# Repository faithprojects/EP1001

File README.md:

# Singapore Polytechnic EP1001 - Further Digital Fabrication & Prototyping Elective Module
Project Website Documentation for EP1001 <br>
A documentation of my school assignments, final project and my journey in undertaking my elective module. <br>
Website link: https://faithprojects.github.io/EP1001/

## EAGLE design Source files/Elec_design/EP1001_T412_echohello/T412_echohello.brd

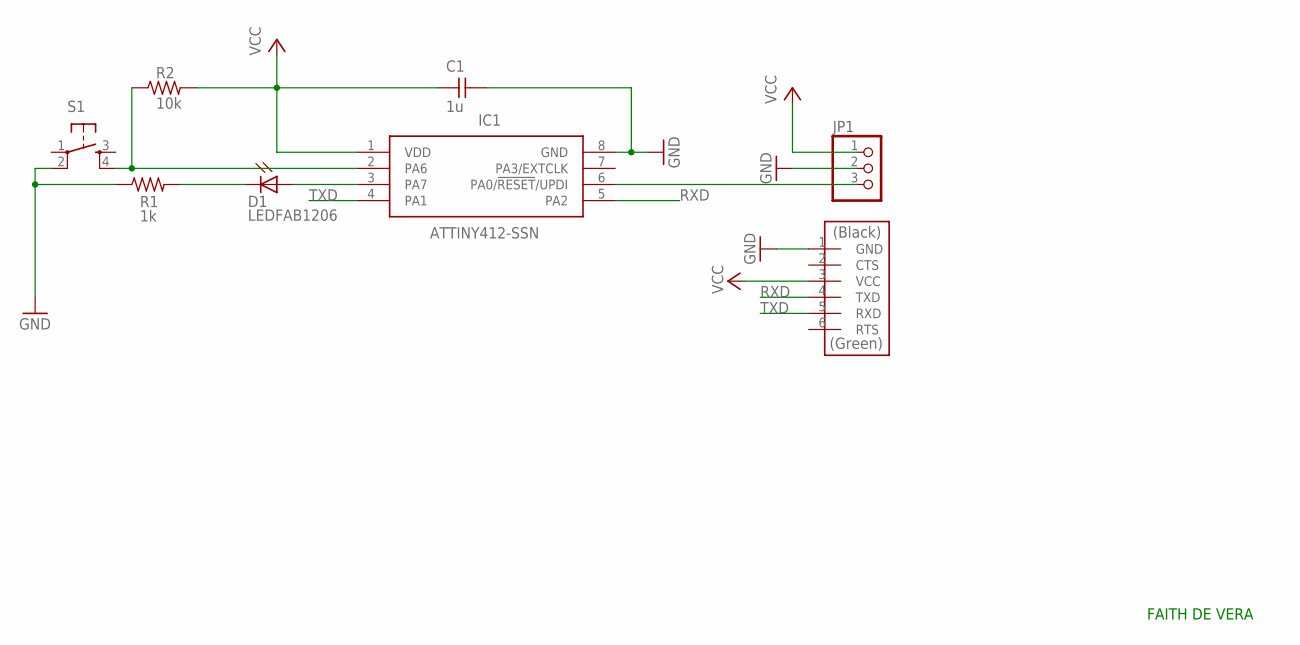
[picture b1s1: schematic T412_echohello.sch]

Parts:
C1: 1u; C1206FAB
D1: LEDFAB1206; LED1206FAB
IC1: ATTINY412-SSN; SOIC127P600X175-8N
JP1: PINHD-1X3; 1X03
R1: 1k; R1206FAB
R2: 10k; R1206FAB
S1: SW_SWITCH_TACTILE_6MM6MM_SWITCH; 6MM_SWITCH
U$2: CONN_06_FTDI-SMD-HEADER; 1X06SMD

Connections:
GND: C1.2, IC1.8 (GND), JP1.2, R1.1, S1.2 (P1), U$2.1 (GND)
unnamed: D1.1 (A), IC1.3 (PA7)
unnamed: D1.2 (C), R1.2
unnamed: IC1.2 (PA6), R2.1, S1.4 (S1)
unnamed: IC1.6 (PA0/!RESET!/UPDI), JP1.3
RXD: IC1.5 (PA2), U$2.4 (TXD)
TXD: IC1.4 (PA1), U$2.5 (RXD)
VCC: C1.1, IC1.1 (VDD), JP1.1, R2.2, U$2.3 (VCC)

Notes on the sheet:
FAITH DE VERA

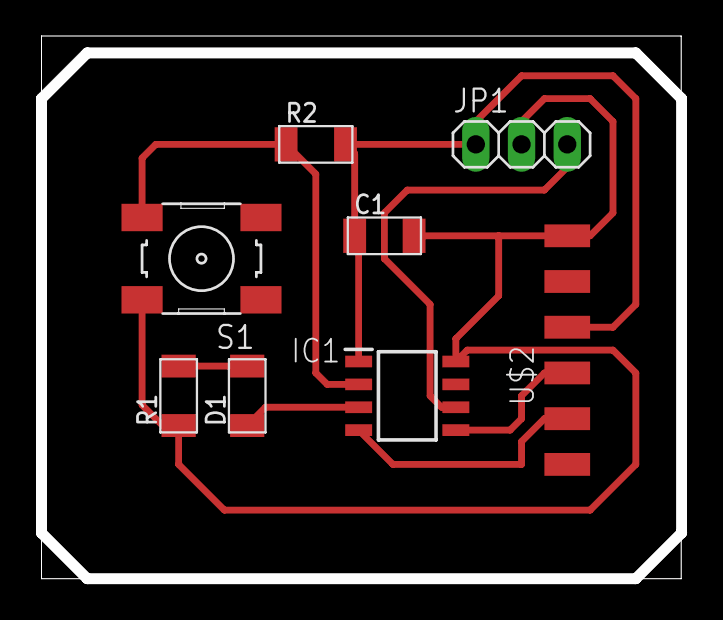
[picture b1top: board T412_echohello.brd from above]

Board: 2 copper layers, 35.5 x 30.1 mm, 8 parts (0 on the bottom side), 8 nets.

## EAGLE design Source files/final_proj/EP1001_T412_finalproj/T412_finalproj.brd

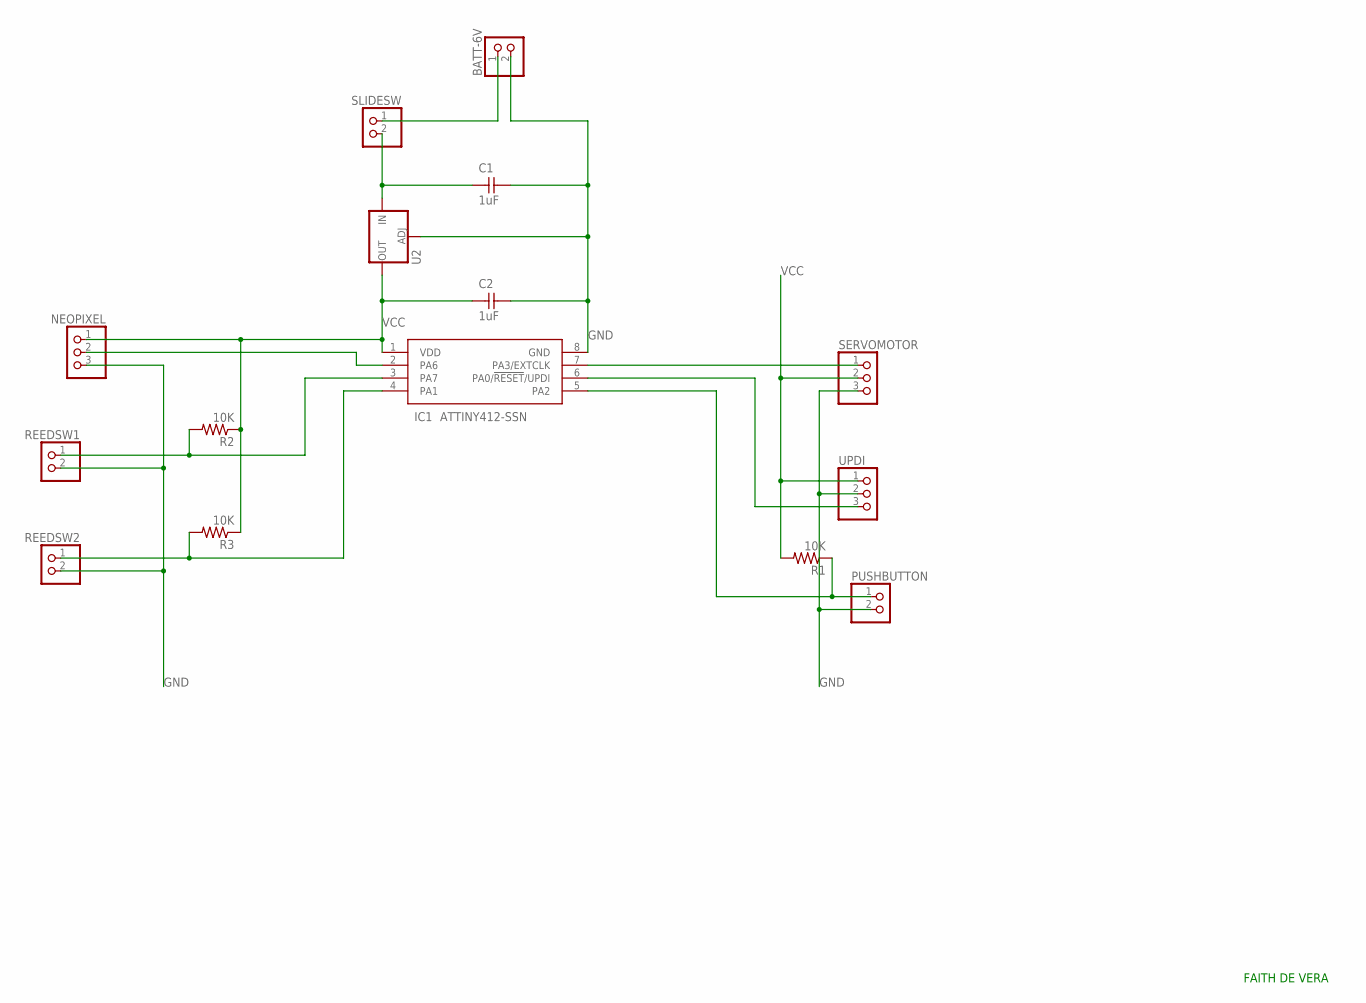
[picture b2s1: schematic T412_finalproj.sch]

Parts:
BATT-6V: PINHD-1X2; 1X02
C1, C2: 1uF; C1206FAB
IC1: ATTINY412-SSN; SOIC127P600X175-8N
NEOPIXEL: PINHD-1X3; 1X03
PUSHBUTTON: PINHD-1X2; 1X02
R1, R2, R3: 10K; R1206FAB
REEDSW1, REEDSW2: PINHD-1X2; 1X02
SERVOMOTOR: PINHD-1X3; 1X03
SLIDESW: PINHD-1X2; 1X02
U2: V_REG_LM1117SOT223; SOT223
UPDI: PINHD-1X3; 1X03

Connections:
GND: BATT-6V.2, C1.2, C2.2, IC1.8 (GND), NEOPIXEL.3, PUSHBUTTON.2, REEDSW1.2, REEDSW2.2, SERVOMOTOR.3, U2.1 (ADJ), UPDI.2
unnamed: IC1.5 (PA2), PUSHBUTTON.1, R1.1
unnamed: IC1.3 (PA7), R2.2, REEDSW1.1
unnamed: IC1.4 (PA1), R3.2, REEDSW2.1
unnamed: IC1.7 (PA3/EXTCLK), SERVOMOTOR.1
unnamed: IC1.6 (PA0/!RESET!/UPDI), UPDI.3
unnamed: C1.1, SLIDESW.2, U2.3 (IN)
unnamed: BATT-6V.1, SLIDESW.1
unnamed: IC1.2 (PA6), NEOPIXEL.2
VCC: C2.1, IC1.1 (VDD), NEOPIXEL.1, R1.2, R2.1, R3.1, SERVOMOTOR.2, U2.2 (OUT), U2.4 (OUT), UPDI.1

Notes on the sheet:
FAITH DE VERA

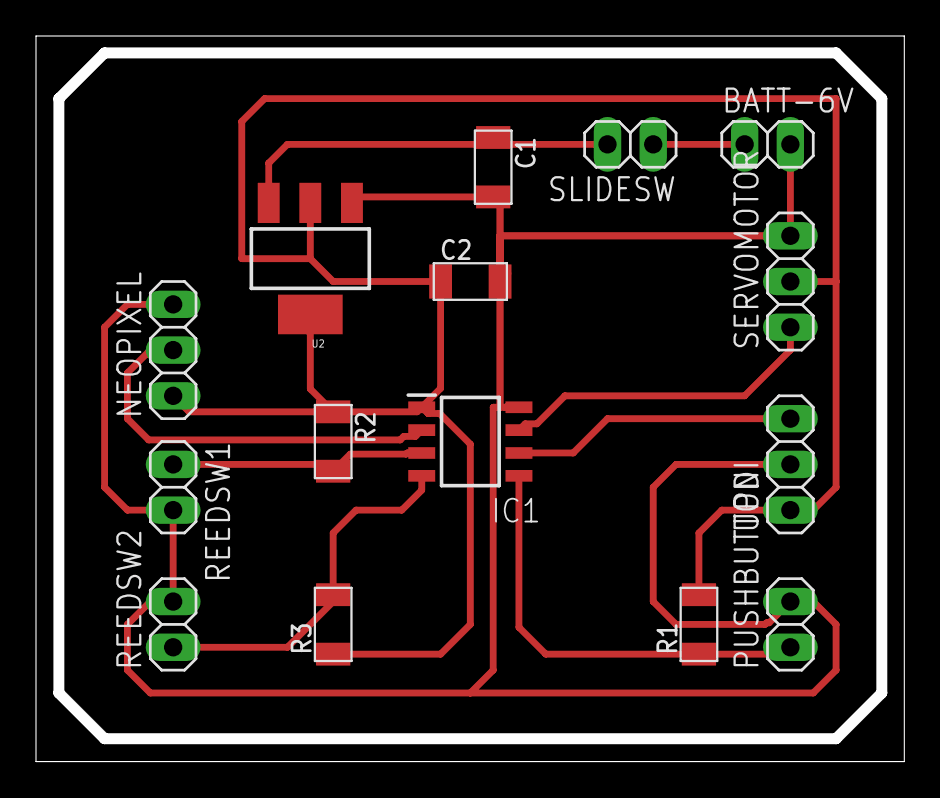
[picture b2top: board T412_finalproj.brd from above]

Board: 2 copper layers, 48.2 x 40.3 mm, 15 parts (0 on the bottom side), 10 nets.

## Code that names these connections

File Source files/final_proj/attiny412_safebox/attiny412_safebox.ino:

//#include <Servo_megaTinyCore.h>

#include <tinyNeoPixel.h>

//Servo myServo;

#define NUMLEDS 10  //Number of Leds on the neopixel strip

#define ledPin PIN_PA6 //Neopixel pin
#define BUTTON PIN_PA2 //Push button pin
#define RPin PIN_PA7   //Reed switch 1 pin
#define RPin2 PIN_PA1  //Reed switch 2 pin
#define ServoPin PIN_PA3  //Servo motor pin

tinyNeoPixel leds = tinyNeoPixel(NUMLEDS, ledPin, NEO_GRB);

int timer;


void setup() {
  //myServo.attach(ServoPin);
  leds.begin();    // initialize the strip
  leds.clear();    //clear the strip
  pinMode(BUTTON, INPUT_PULLUP);
  pinMode(RPin, INPUT_PULLUP);
  pinMode(RPin2, INPUT_PULLUP);
}

void loop() {
  //When the button is pressed, game starts
  if (digitalRead(BUTTON) == LOW){
    delay(15);
    //myServo.write(90);    //Locks the safe door
    //delay(15);
    while (digitalRead(BUTTON) == LOW);
    //Light Sequence when the game starts
    for (int i = 0; i < NUMLEDS; ++i)
    {
      leds.setPixelColor(i, 22, 255, 0);       // LIGHT GREEN
      leds.show();
      delay(200);
      leds.setPixelColor(i, 55, 146, 55);       // GREEN
      leds.show();
    }
    leds.clear();

    //Countdown light sequence
    for (timer =0; timer <= 10; timer++) {
      leds.setPixelColor(timer, 220, 0, 0);       // RED
      leds.show();
      
      int proximity = digitalRead(RPin); // Read the state of the switch
      int proximity2 = digitalRead(RPin2); // Read the state of the switch
      delay(1000);
      
      //If reed switches are on, you win the game
      if (proximity == LOW && proximity2 == LOW) {
        //myServo.write(180);       //Unlocks the safe door
        //delay(15);
        //Light Sequence when you win the game
        for (int i = 0; i < NUMLEDS; ++i)
        {
          leds.setPixelColor(i, 91, 46, 126);       // WHITE
          leds.show();
          delay(200);
          leds.setPixelColor(i, 0, 0, 32);       // BLUE
          leds.show();
        }
        break;
      
      }
      
      else {
        leds.clear();
        leds.show();

        //if timer is already 10 secs, time's up!
        if (timer == 10) {
          //Light Sequence when you failed the game
          for (int i = 0; i < NUMLEDS; ++i)
          {
            leds.setPixelColor(i, 255, 139, 19);       // RED
            leds.show();
            delay(200);
            leds.setPixelColor(i, 250, 171, 120);       // BLUE
            leds.show();
          }
        }
      }
      
      delay(1000);
      
    }
  }
  else {
    delay(1000);
  }
  
  
}

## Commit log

2023-01-05 Added html and css files
2023-01-05 adding images part 1
2023-01-05 adding more images part 2
2023-01-05 added more images part 3
2023-01-05 update on size of the page
2023-01-05 Revert back to og size
2023-01-05 Update the electronicc design images
2023-01-23 Added new pages for documentation
2023-01-23 Added a new nav item for final project
2023-01-23 Added the styles for the new pages
2023-01-23 edited the nav bar
2023-01-23 edited nav bar and added website links
2023-01-23 Edit Readme
2023-01-23 updated the css
2023-01-23 molding and casting images
2023-01-23 added star nc file image
2023-01-23 Updated mold and casting
2023-01-23 edited the link for stepcraft cnc
2023-01-27 new svg images
2023-01-27 updated some html files
2023-02-05 added images
    for cnc, final project and electronic design
2023-02-17 New images added
2023-02-17 Final project bookmarks
2023-02-17 new images
2023-02-17 added more image sizes
2023-02-17 updated the image sizing
2023-02-17 new images for final proj
2023-02-17 Adding stuff into the final project
2023-02-20 fix a typo error
2023-02-20 edited images
2023-02-20 new image added
2023-02-20 update embedded prog pic
2023-02-20 images added and edited
2023-02-21 Added my source files for all my projects
2023-02-21 Materials done and CAD modelling added
2023-02-22 adding more source files
2023-02-22 Added some new source files and updated others
2023-02-22 added files section
2023-02-22 added interface programming image
2023-02-22 added new images for interface prog
2023-02-22 added new source file for interface
2023-02-23 Putting in new source files
2023-02-23 update the files section
2023-02-23 Update files section and edit text
2023-02-23 removed some svg images
2023-02-23 Update the icons
2023-02-23 update the images
2023-02-23 Editing some text and image sizes
2023-02-24 Changed the file downloads
2023-02-24 Change all source files to zip
2023-02-24 Change file links

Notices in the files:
parts and their libraries:
SparkFun-IC-Power: Licensing: Creative Commons ShareAlike 4.0 International - https://creativecommons.org/licenses/by-sa/4.0
